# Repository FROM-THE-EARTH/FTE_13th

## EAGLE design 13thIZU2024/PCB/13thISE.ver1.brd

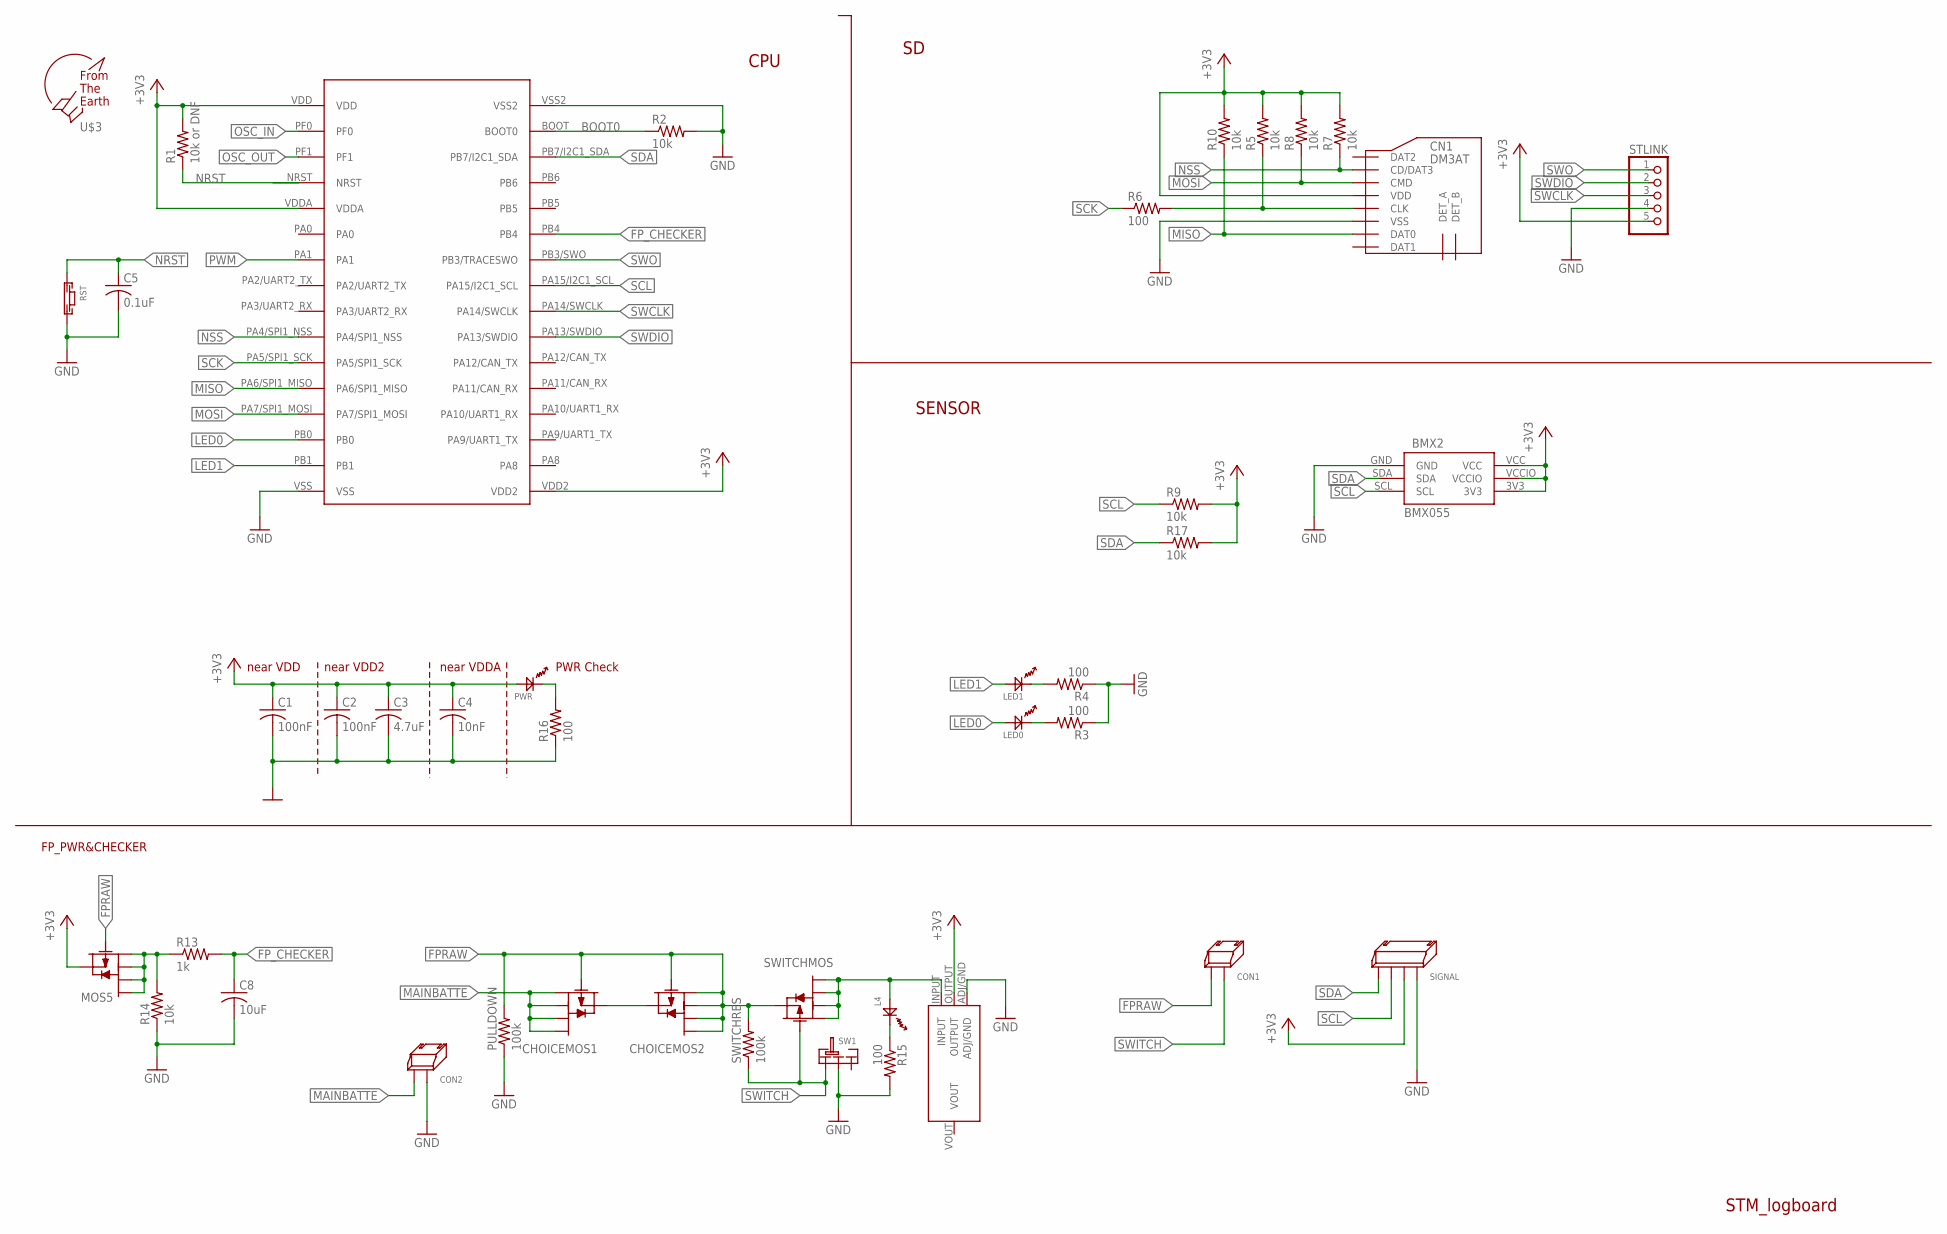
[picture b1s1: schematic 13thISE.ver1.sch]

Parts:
BMX2: BMX055
C1, C2: 100nF; C1608
C3: 4.7uF; C1608
C4: 10nF; C1608
C5: 0.1uF; C1608
C8: 10uF; C0603
CHOICEMOS1, CHOICEMOS2: PCH_SSM6J808R; SSM6J808R
CN1: DM3AT
CON1, CON2: 2PIN_SIDE
L4: OSXX1608C1A
LED0, LED1: OSXX1608C1A
MOS5: PCH_SSM6J808R; SSM6J808R
PULLDOWN: 100k; R0603
PWR: OSXX1608C1A
R1: 10k or DNF; R0603
R2, R5, R7, R8, R9, R10, R14, R17: 10k; R0603
R3, R4, R6, R15, R16: 100; R0603
R13: 1k; R0603
RST: TVAF06-A020B-R
SIGNAL: 4PIN_SIDE
STLINK: PINHD-1X5/90; 1X05/90
SW1: SRIDE_SWITCH
SWITCHMOS: PCH_SSM6J808R; SSM6J808R
SWITCHRES: 100k; R0603
U$1: STM32F303K8
U$3: F.T.E.LOGO; LOGO
U$4: AZ1117C

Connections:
+3V3: BMX2.3V3, BMX2.VCC, BMX2.VCCIO, C1.1, C2.1, C3.1, C4.1, CN1.VDD, MOS5.4, PWR.AN, R1.2, R5.2, R7.2, R8.2, R9.2, R10.2, R17.2, SIGNAL.P$3, STLINK.5, U$1.VDD, U$1.VDD2, U$1.VDDA, U$4.OUTPUT
BOOT0: R2.1, U$1.BOOT (BOOT0)
FPRAW: CHOICEMOS1.3, CHOICEMOS2.1, CHOICEMOS2.2, CHOICEMOS2.3, CHOICEMOS2.5, CHOICEMOS2.6, CON1.P$2, MOS5.3, PULLDOWN.2, SWITCHMOS.4, SWITCHRES.2
FP_CHECKER: C8.1, R13.2, U$1.PB4
GND: BMX2.GND, C1.2, C2.2, C3.2, C4.2, C5.2, C8.2, CN1.VSS, CON2.P$1, PULLDOWN.1, R2.2, R3.1, R4.1, R14.1, R15.2, R16.1, RST.P$2, SIGNAL.P$4, STLINK.4, SW1.LR, U$1.VSS, U$1.VSS2, U$4.ADJ/GND
LED0: LED0.AN, U$1.PB0
LED1: LED1.AN, U$1.PB1
MAINBATTE: CHOICEMOS1.1, CHOICEMOS1.2, CHOICEMOS1.5, CHOICEMOS1.6, CON2.P$2
MISO: CN1.DAT0, R10.1, U$1.PA6/SPI1_MISO
MOSI: CN1.CMD, R8.1, U$1.PA7/SPI1_MOSI
unnamed: PWR.CT, R16.2
unnamed: LED0.CT, R3.2
unnamed: LED1.CT, R4.2
unnamed: CN1.CLK, R5.1, R6.2
unnamed: CHOICEMOS1.4, CHOICEMOS2.4
unnamed: L4.AN, SWITCHMOS.1, SWITCHMOS.2, SWITCHMOS.5, SWITCHMOS.6, U$4.INPUT
unnamed: MOS5.1, MOS5.2, MOS5.5, MOS5.6, R13.1, R14.2
unnamed: L4.CT, R15.1
NRST: C5.1, R1.1, RST.P$1
NSS: CN1.CD/DAT3, R7.1, U$1.PA4/SPI1_NSS
OSC_IN: U$1.PF0
OSC_OUT: U$1.PF1
PWM: U$1.PA1
SCK: R6.1, U$1.PA5/SPI1_SCK
SCL: BMX2.SCL, R9.1, SIGNAL.P$1, U$1.PA15/I2C1_SCL
SDA: BMX2.SDA, R17.1, SIGNAL.P$2, U$1.PB7/I2C1_SDA
SWCLK: STLINK.3, U$1.PA14/SWCLK
SWDIO: STLINK.2, U$1.PA13/SWDIO
SWITCH: CON1.P$1, SW1.L, SWITCHMOS.3, SWITCHRES.1
SWO: STLINK.1, U$1.PB3/SWO (PB3/TRACESWO)

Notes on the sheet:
near VDD
near VDD2
near VDDA
PWR Check
STM_logboard
CPU
FP_PWR&CHECKER
SENSOR

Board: 2 copper layers, 42 parts (0 on the bottom side), 27 nets, no tracks yet.

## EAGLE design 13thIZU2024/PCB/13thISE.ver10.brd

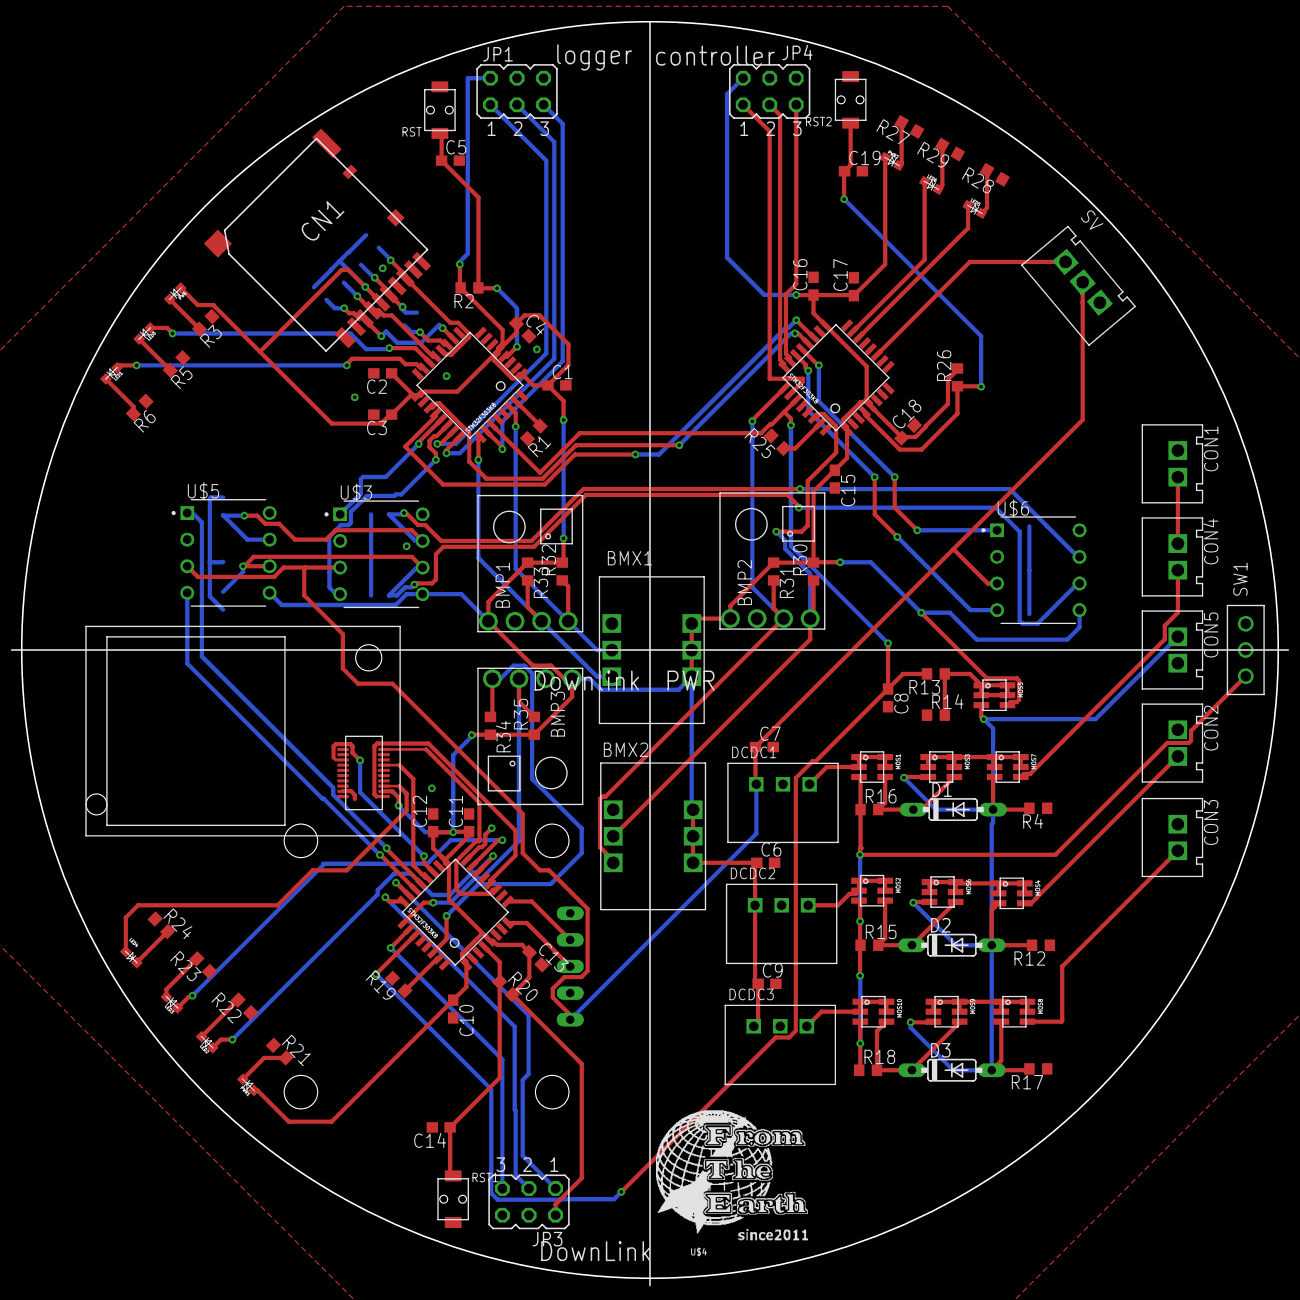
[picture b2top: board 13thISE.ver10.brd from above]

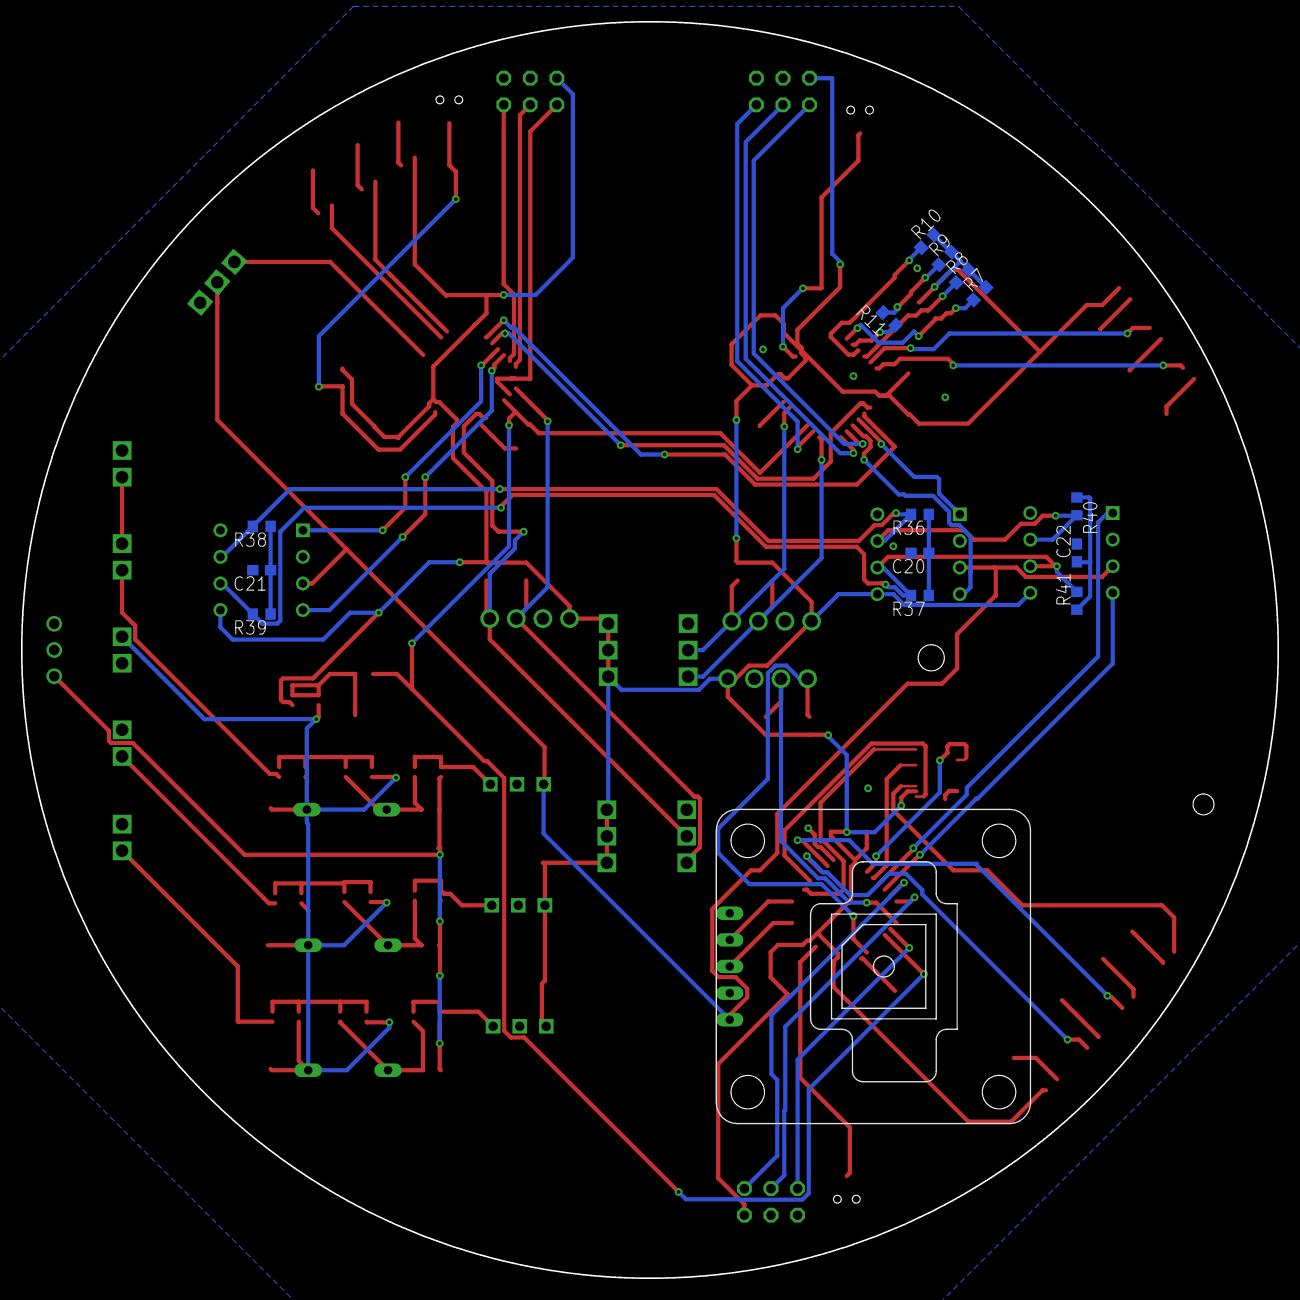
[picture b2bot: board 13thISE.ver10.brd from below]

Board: 2 copper layers, 120.0 x 120.0 mm, 117 parts (15 on the bottom side), 83 nets.

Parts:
BMP1, BMP2, BMP3: BMP180; GY-68
BMX1, BMX2: BMX055
C1, C2, C10, C11, C15, C16: 100nF; C1608
C3, C12, C17: 4.7uF; C1608
C4, C13, C18: 10nF; C1608
C5, C14, C19: 0.1uF; C1608
C6, C7, C9: 3.3uF; C0603
C8: 10uF; C0603
C20, C21, C22: 4.7nF; C0603
CN1: DM3AT
CON1, CON2, CON3, CON4, CON5: 2PIN
D1, D2, D3: 1N4148DO35-7; DO35-7
DCDC1: 5V1A_M78AR05-1
DCDC2, DCDC3: 3.3V1A_M78AR033-1
IM1: IM920_IM920C
JP1, JP3, JP4: JP3Q
LED0, LED1, LED2, LED3, LED4, LED5, LED6: OSXX1608C1A
MOS1, MOS2, MOS3, MOS4, MOS5, MOS6, MOS7, MOS8, MOS9, MOS10: SSM6J808R
PWR, PWR1, PWR2: OSXX1608C1A
R1, R7, R8, R9, R10, R14, R19, R25, R30, R31, R32, R33, R34, R35: 10k; R0603
R2, R20, R26: 10k or DNF; R0603
R3, R5, R6, R11, R21, R22, R23, R24, R27, R28, R29: 100; R0603
R4, R12, R13, R17: 1k; R0603
R15, R16, R18: 100k; R0603
R36, R37, R38, R39, R40, R41: 60; R0603
RST, RST1, RST2: TVAF06-A020B-R
STM0, STM1: STM32F303K8
SV: 3PIN
SW1: SRIDE_SWITCH
U$1: STM32F303K8
U$2: AE-GYSFDMAXB
U$3, U$5, U$6: DIP762W45P254L949H533Q8B
U$4: F.T.E.LOGO; LOGO

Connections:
3.3_RAW1: CON4.P$2, MOS7.4
3.3_RAW2: CON1.P$2, CON4.P$1
3.3_RAW3: CON2.P$2, MOS4.4
3.3_RAW4: CON3.P$2, MOS8.4
+3V3: BMP1.P1, BMP2.P1, BMP3.P1, BMX1.3V3, BMX1.VCC, BMX1.VCCIO, BMX2.3V3, BMX2.VCC, BMX2.VCCIO, C1.1, C2.1, C3.1, C4.1, C6.1, C9.1, C10.1, C11.1, C12.1, C13.1, C15.1, C16.1, C17.1, C18.1, CN1.VDD, DCDC2.VOUT, DCDC3.VOUT, IM1.$P17, JP1.2, JP3.2, JP4.2, MOS5.4, PWR.AN, PWR1.AN, PWR2.AN, R2.2, R7.2, R8.2, R9.2, R10.2, R20.2, R26.2, R30.2, R31.1, R32.2, R33.1, R34.2, R35.1, STM0.VDD, STM0.VDD2, STM0.VDDA, STM1.VDD, STM1.VDD2, STM1.VDDA, U$1.VDD, U$1.VDD2, U$1.VDDA, U$3.5, U$5.5, U$6.5
+5V: C7.1, DCDC1.VOUT, SV.P$2, U$2.P1, U$3.3, U$5.3, U$6.3
+5V1: DCDC1.VIN, MOS1.1, MOS1.2, MOS1.5, MOS1.6
BOOT0: R1.1, STM0.BOOT
BOOT1: R19.1, STM1.BOOT
BOOT2: R25.1, U$1.BOOT
CANH: R36.2, R38.2, R40.2, U$3.7, U$5.7, U$6.7
CANL: R37.2, R39.2, R41.2, U$3.6, U$5.6, U$6.6
FP: CON5.P$1, D1.A, D2.A, D3.A, MOS3.3, MOS4.3, MOS5.3, MOS6.3, MOS7.3, MOS8.3, MOS9.3, R4.2, R12.2, R17.2
FP_CHECKER: C8.1, R13.2, STM0.PB4, STM1.PB4, U$1.PB4
GND: BMP1.P2, BMP2.P2, BMP3.P2, BMX1.GND, BMX2.GND, C1.2, C2.2, C3.2, C4.2, C5.2, C6.2, C7.2, C8.2, C9.2, C10.2, C11.2, C12.2, C13.2, C14.2, C15.2, C16.2, C17.2, C18.2, C19.2, C20.2, C21.2, C22.2, CN1.VSS, CON1.P$1, CON2.P$1, CON3.P$1, CON5.P$2, DCDC1.GND, DCDC2.GND, DCDC3.GND, IM1.$P18, JP1.6, JP3.6, JP4.6, R1.2, R3.1, R4.1, R5.1, R6.1, R12.1, R14.1, R17.1, R19.2, R21.1, R22.1, R23.1, R24.1, R25.2, R27.1, R28.1, R29.1, RST.P$2, RST1.P$2, RST2.P$2, STM0.VSS, STM0.VSS2, STM1.VSS, STM1.VSS2, SV.P$3, SW1.LR, U$1.VSS, U$1.VSS2, U$2.P2, U$3.2, U$3.8, U$5.2, U$5.8, U$6.2, U$6.8
GPSRX: STM1.PA2/UART2_TX, U$2.P3
GPSTX: STM1.PA3/UART2_RX, U$2.P4
IM_BUSY: IM1.$P1, STM1.PA5/SPI1_SCK
IM_RESET: IM1.$P19, STM1.PA6/SPI1_MISO
IM_RX: IM1.$P6, STM1.PA9/UART1_TX
IM_TX: IM1.$P7, STM1.PA10/UART1_RX
LED: IM1.$P15, LED4.AN
LED0: LED0.AN, STM0.PB0
LED1: LED1.AN, STM0.PB1
LED1.0: LED2.AN, STM1.PB0
LED1.1: LED3.AN, STM1.PB1
LED2.0: LED5.AN, U$1.PB0
LED2.1: LED6.AN, U$1.PB1
LOGRX: STM0.PA9/UART1_TX, U$1.PA10/UART1_RX
LOGTX: STM0.PA10/UART1_RX, U$1.PA9/UART1_TX
MISO: CN1.DAT0, R10.1, STM0.PA6/SPI1_MISO
MOSI: CN1.CMD, R8.1, STM0.PA7/SPI1_MOSI
unnamed: PWR.CT, R3.2
unnamed: LED0.CT, R5.2
unnamed: D1.C, MOS1.4, MOS3.4, R16.2
unnamed: LED1.CT, R6.2
unnamed: D2.C, MOS2.4, MOS6.4, R15.2
unnamed: MOS4.1, MOS4.2, MOS4.5, MOS4.6, MOS6.1, MOS6.2, MOS6.5, MOS6.6
unnamed: CN1.CLK, R9.1, R11.2
unnamed: DCDC2.VIN, MOS2.1, MOS2.2, MOS2.5, MOS2.6
unnamed: D3.C, MOS9.4, MOS10.4, R18.2
unnamed: MOS8.1, MOS8.2, MOS8.5, MOS8.6, MOS9.1, MOS9.2, MOS9.5, MOS9.6
unnamed: PWR2.CT, R27.2
unnamed: MOS3.1, MOS3.2, MOS3.5, MOS3.6, MOS7.1, MOS7.2, MOS7.5, MOS7.6
unnamed: DCDC3.VIN, MOS10.1, MOS10.2, MOS10.5, MOS10.6
unnamed: MOS5.1, MOS5.2, MOS5.5, MOS5.6, R13.1, R14.2
unnamed: PWR1.CT, R21.2
unnamed: LED2.CT, R22.2
unnamed: LED3.CT, R23.2
unnamed: LED4.CT, R24.2
unnamed: LED5.CT, R28.2
unnamed: LED6.CT, R29.2
unnamed: C21.1, R38.1, R39.1
unnamed: C22.1, R40.1, R41.1
unnamed: C20.1, R36.1, R37.1
NRST0: C5.1, R2.1, RST.P$1, STM0.NRST
NRST1: C14.1, R20.1, RST1.P$1, STM1.NRST
NRST2: C19.1, R26.1, RST2.P$1, U$1.NRST
NSS: CN1.CD/DAT3, R7.1, STM0.PA4/SPI1_NSS
PWM: SV.P$1, U$1.PA5/SPI1_SCK
RXCAN: STM0.PA12/CAN_TX, U$3.4
RXCAN1: STM1.PA12/CAN_TX, U$5.4
RXCAN2: U$1.PA12/CAN_TX, U$6.4
SCK: R11.1, STM0.PA5/SPI1_SCK
SCL0: BMP1.P3, BMX1.SCL, R33.2, STM0.PA15/I2C1_SCL
SCL1: BMP3.P3, R35.2, STM1.PA15/I2C1_SCL
SCL2: BMP2.P3, BMX2.SCL, R31.2, U$1.PA15/I2C1_SCL
SDA0: BMP1.P4, BMX1.SDA, R32.1, STM0.PB7/I2C1_SDA
SDA1: BMP3.P4, R34.1, STM1.PB7/I2C1_SDA
SDA2: BMP2.P4, BMX2.SDA, R30.1, U$1.PB7/I2C1_SDA
SW: MOS1.3, MOS2.3, MOS10.3, R15.1, R16.1, R18.1, SW1.L
SWCLK: JP1.3, STM0.PA14/SWCLK
SWCLK1: JP3.3, STM1.PA14/SWCLK
SWCLK2: JP4.3, U$1.PA14/SWCLK
SWDIO: JP1.1, STM0.PA13/SWDIO
SWDIO1: JP3.1, STM1.PA13/SWDIO
SWDIO2: JP4.5, U$1.PA13/SWDIO
SWO: JP1.5, STM0.PB3/SWO
SWO1: JP3.5, STM1.PB3/SWO
SWO2: JP4.1, U$1.PB3/SWO
TXCAN: STM0.PA11/CAN_RX, U$3.1
TXCAN1: STM1.PA11/CAN_RX, U$5.1
TXCAN2: U$1.PA11/CAN_RX, U$6.1
